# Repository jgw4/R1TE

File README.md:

# Replica-1-TE

This repository is a fork of The Original Replica 1 TE-3, with the addition of a KiCad re-building of the PCB using the native schematic and and pcb editors. This makes it easier for those willing to modify the Replica-1 to suit their particular custom replica-1. This repo will eventually become the basis for the uA1 stripped down Apple-1 clone.

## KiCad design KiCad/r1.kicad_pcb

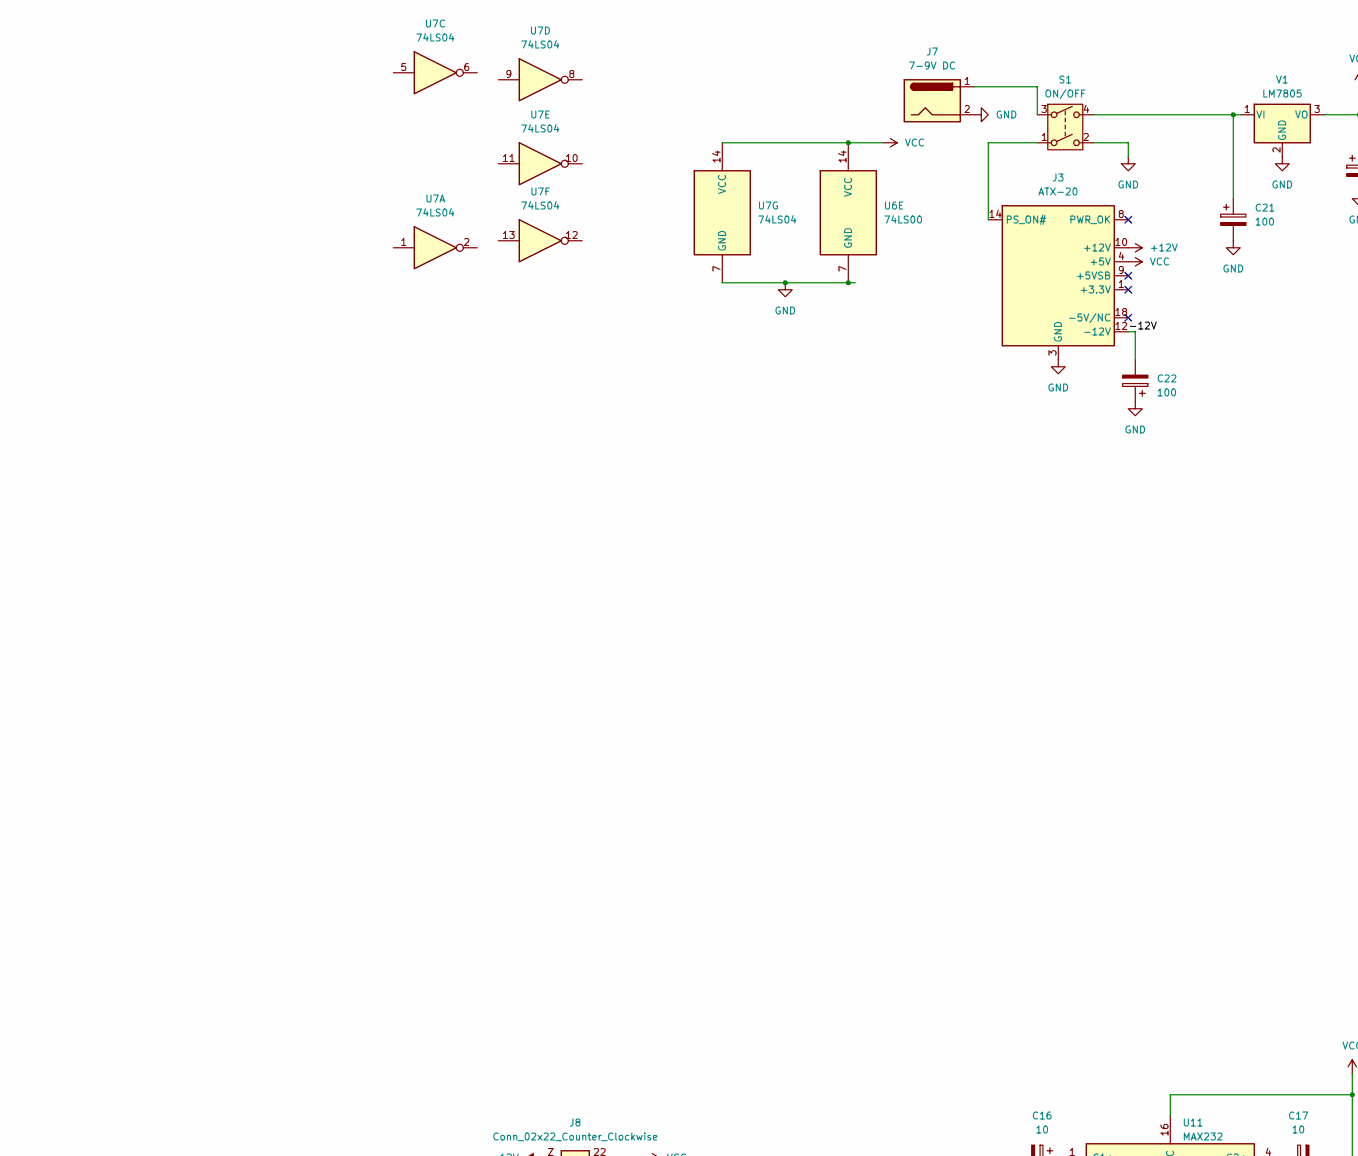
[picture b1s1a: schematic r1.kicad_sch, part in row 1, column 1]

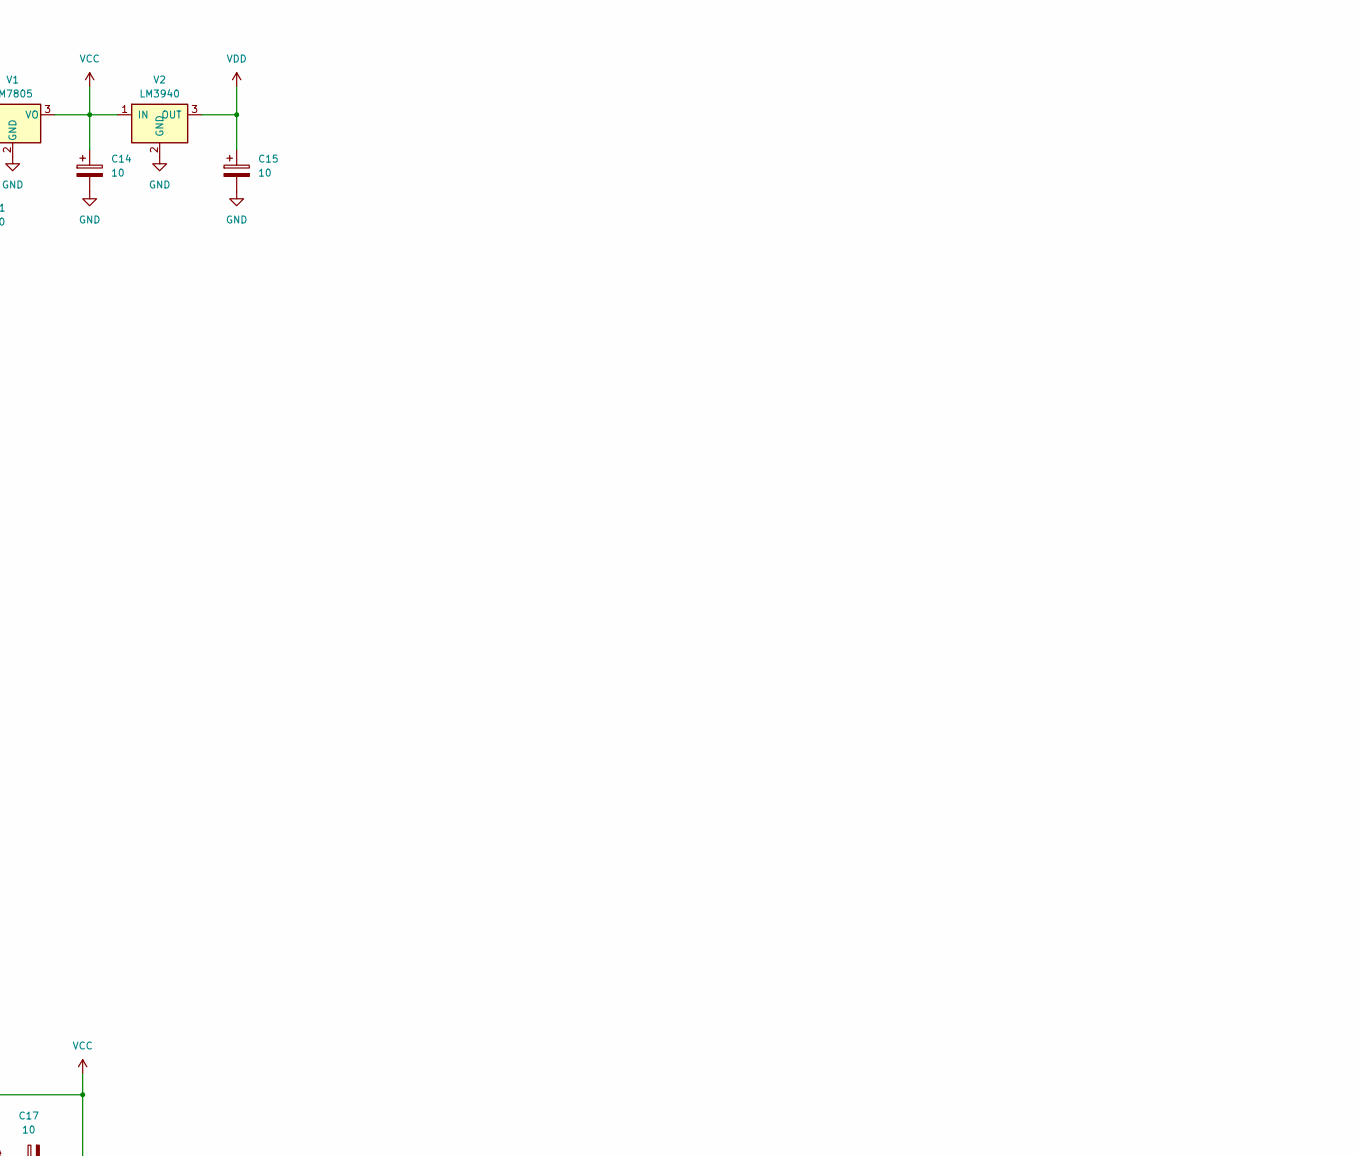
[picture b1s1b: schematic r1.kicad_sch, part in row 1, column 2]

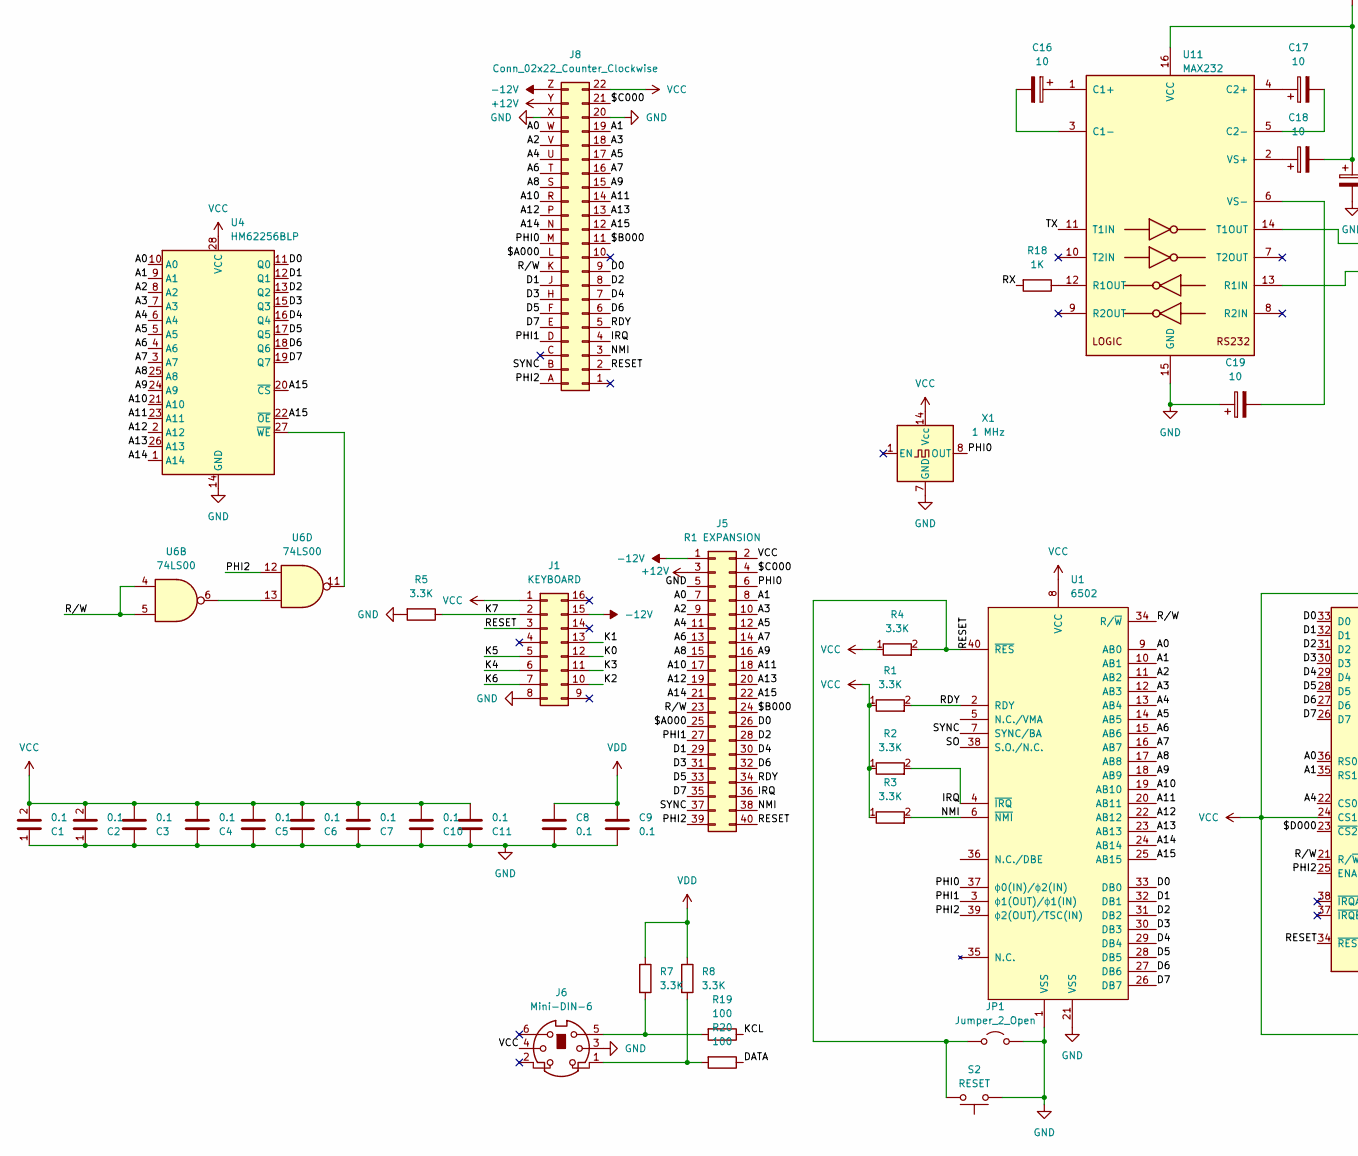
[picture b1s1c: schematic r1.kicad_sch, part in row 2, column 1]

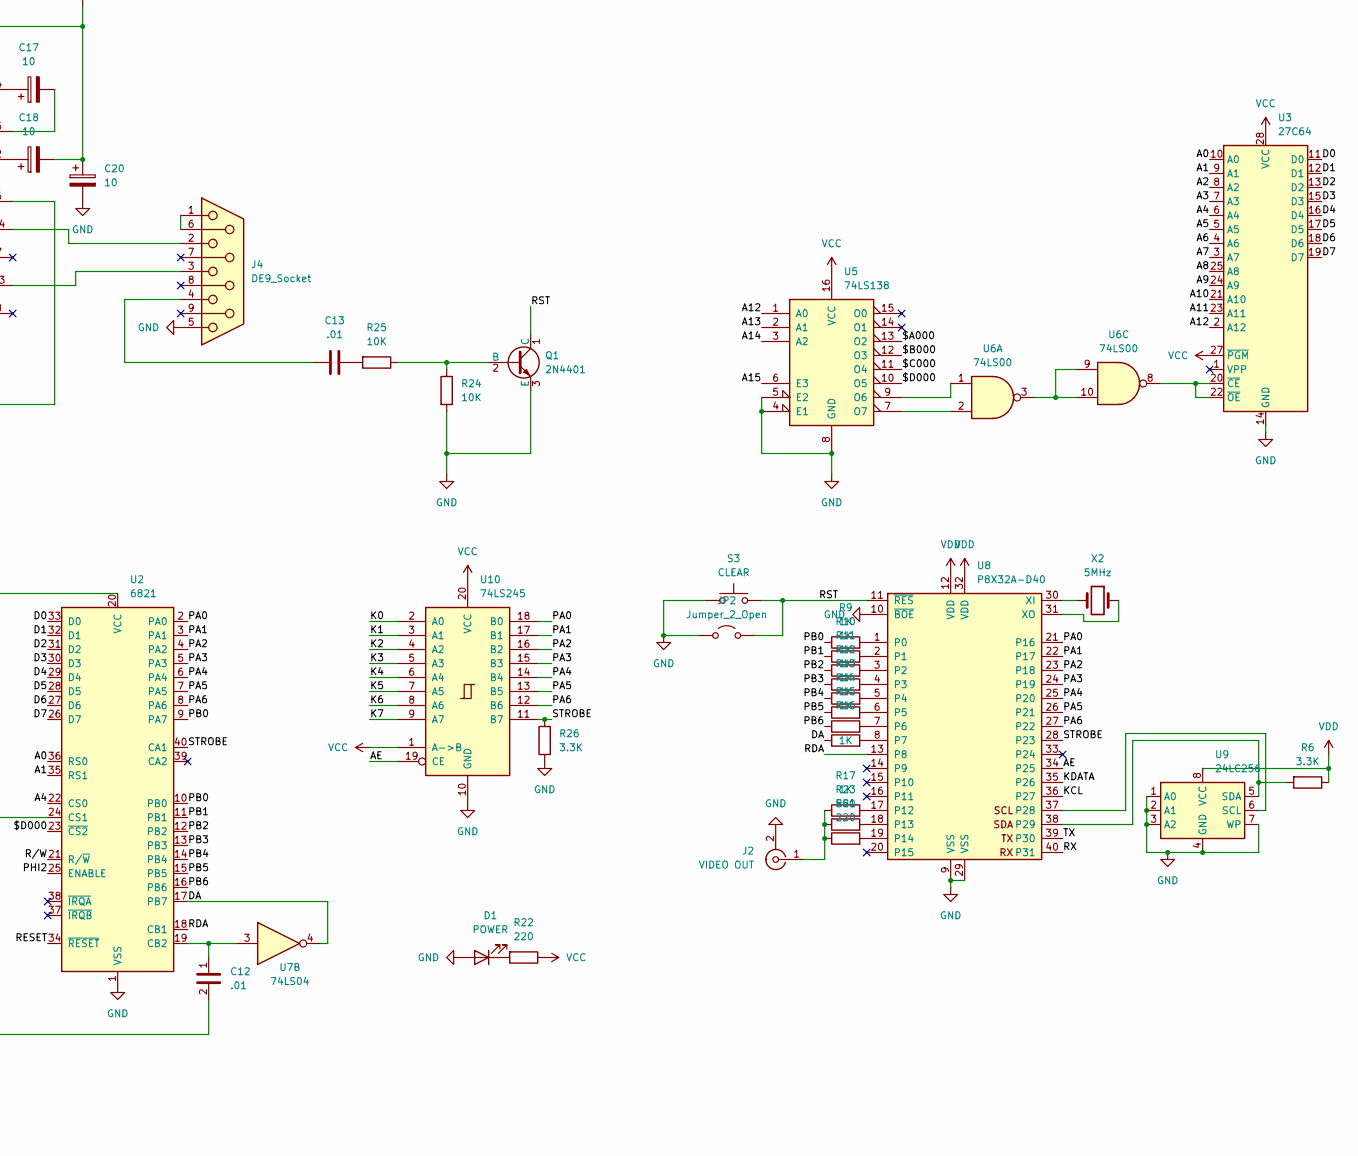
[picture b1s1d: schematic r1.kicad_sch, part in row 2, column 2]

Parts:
C1, C2, C3, C4, C5, C6, C7, C8, C9, C10, C11: 0.1; C_Disc_D7.0mm_W2.5mm_P5.00mm
C12, C13: .01; C_Disc_D7.0mm_W2.5mm_P5.00mm
C14, C15, C16, C17, C18, C19, C20: 10; CP_Radial_D5.0mm_P2.00mm
C21: 100; CP_Radial_D10.0mm_P5.00mm
C22: 100; CP_Radial_D5.0mm_P2.00mm
D1: POWER; LED_D5.0mm
J1: KEYBOARD; DIP-16_W7.62mm_Socket_LongPads
J2: VIDEO OUT; Keystone 901
J3: ATX-20; Molex_Mini-Fit_Jr_5566-20A2_2x10_P4.20mm_Vertical
J4: DE9_Socket; DSUB-9_Socket_Horizontal_P2.77x2.84mm_EdgePinOffset7.70mm_H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
J5: R1 EXPANSION; PinHeader_2x20_P2.54mm_Vertical
J6: Mini-DIN-6
J7: 7-9V DC; BarrelJack_GCT_DCJ200-10-A_Horizontal
J8: Conn_02x22_Counter_Clockwise; CardEdgeConnector_44p_P156mils
JP1, JP2: Jumper_2_Open; TestPoint_Bridge_Pitch2.54mm_Drill1.0mm
Q1: 2N4401; TO-92_Inline_Wide
R1, R2, R3, R4, R5, R6, R7, R8, R26: 3.3K; R_Axial_DIN0207_L6.3mm_D2.5mm_P10.16mm_Horizontal
R9, R10, R11, R12, R13, R14, R15, R16, R17, R18: 1K; R_Axial_DIN0207_L6.3mm_D2.5mm_P10.16mm_Horizontal
R19, R20: 100; R_Axial_DIN0207_L6.3mm_D2.5mm_P10.16mm_Horizontal
R21, R22: 220; R_Axial_DIN0207_L6.3mm_D2.5mm_P10.16mm_Horizontal
R23: 560; R_Axial_DIN0207_L6.3mm_D2.5mm_P10.16mm_Horizontal
R24, R25: 10K; R_Axial_DIN0207_L6.3mm_D2.5mm_P10.16mm_Horizontal
S1: ON/OFF; ToggleSW_DPDT_VerticalPC
S2: RESET; SW_PUSH_6mm
S3: CLEAR; SW_PUSH_6mm
U1: 6502; DIP-40_W15.24mm_Socket_LongPads
U2: 6821; DIP-40_W15.24mm_Socket_LongPads
U3: 27C64; DIP-28_W15.24mm_Socket_LongPads
U4: HM62256BLP; DIP-28_W15.24mm_Socket_LongPads
U5: 74LS138; DIP-16_W7.62mm_Socket_LongPads
U6: 74LS00; DIP-14_W7.62mm_Socket_LongPads
U7: 74LS04; DIP-14_W7.62mm_Socket_LongPads
U8: P8X32A-D40; DIP-40_W15.24mm_Socket_LongPads
U9: 24LC256; DIP-8_W7.62mm_Socket_LongPads
U10: 74LS245; DIP-20_W7.62mm_Socket_LongPads
U11: MAX232; DIP-16_W7.62mm_Socket_LongPads
V1: LM7805; TO-220-3_Horizontal_TabDown
V2: LM3940; TO-220-3_Horizontal_TabDown
X1: 1 MHz; Oscillator_DIP-14
X2: 5MHz; Crystal_HC18-U_Vertical

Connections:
+12V: J3.10 (+12V), J5.3, J8.Y
-12V: C22.2, J1.15, J3.12 (-12V), J5.1, J8.Z
/$A000: J5.25, J8.L (Pin_3L), U5.13 (O2)
/$B000: J5.24, J8.11, U5.12 (O3)
/$C000: J5.4, J8.21, U5.11 (O4)
/$D000: U2.23 (~CS2), U5.10 (O5)
/A0: J5.7, J8.W, U1.9 (AB0), U2.36 (RS0), U3.10 (A0), U4.10 (A0)
/A1: J5.8, J8.19, U1.10 (AB1), U2.35 (RS1), U3.9 (A1), U4.9 (A1)
/A2: J5.9, J8.V, U1.11 (AB2), U3.8 (A2), U4.8 (A2)
/A3: J5.10, J8.18, U1.12 (AB3), U3.7 (A3), U4.7 (A3)
/A4: J5.11, J8.U, U1.13 (AB4), U2.22 (CS0), U3.6 (A4), U4.6 (A4)
/A5: J5.12, J8.17, U1.14 (AB5), U3.5 (A5), U4.5 (A5)
/A6: J5.13, J8.T, U1.15 (AB6), U3.4 (A6), U4.4 (A6)
/A7: J5.14, J8.16, U1.16 (AB7), U3.3 (A7), U4.3 (A7)
/A8: J5.15, J8.S, U1.17 (AB8), U3.25 (A8), U4.25 (A8)
/A9: J5.16, J8.15, U1.18 (AB9), U3.24 (A9), U4.24 (A9)
/A10: J5.17, J8.R, U1.19 (AB10), U3.21 (A10), U4.21 (A10)
/A11: J5.18, J8.14, U1.20 (AB11), U3.23 (A11), U4.23 (A11)
/A12: J5.19, J8.P, U1.22 (AB12), U3.2 (A12), U4.2 (A12), U5.1 (A0)
/A13: J5.20, J8.13, U1.23 (AB13), U4.26 (A13), U5.2 (A1)
/A14: J5.21, J8.N, U1.24 (AB14), U4.1 (A14), U5.3 (A2)
/A15: J5.22, J8.12, U1.25 (AB15), U4.20 (~CS), U4.22 (~OE), U5.6 (E3)
/AE: U8.34 (P25), U10.19 (CE)
/D0: J5.26, J8.9, U1.33 (DB0), U2.33 (D0), U3.11 (D0), U4.11 (Q0)
/D1: J5.29, J8.J, U1.32 (DB1), U2.32 (D1), U3.12 (D1), U4.12 (Q1)
/D2: J5.28, J8.8, U1.31 (DB2), U2.31 (D2), U3.13 (D2), U4.13 (Q2)
/D3: J5.31, J8.H, U1.30 (DB3), U2.30 (D3), U3.15 (D3), U4.15 (Q3)
/D4: J5.30, J8.7, U1.29 (DB4), U2.29 (D4), U3.16 (D4), U4.16 (Q4)
/D5: J5.33, J8.F, U1.28 (DB5), U2.28 (D5), U3.17 (D5), U4.17 (Q5)
/D6: J5.32, J8.6, U1.27 (DB6), U2.27 (D6), U3.18 (D6), U4.18 (Q6)
/D7: J5.35, J8.E, U1.26 (DB7), U2.26 (D7), U3.19 (D7), U4.19 (Q7)
/DA: R16.1, U2.17 (PB7), U7.4
/DATA: R20.1
/IRQ: J5.36, J8.4, R2.2, U1.4 (~IRQ)
/K0: J1.12, U10.2 (A0)
/K1: J1.13, U10.3 (A1)
/K2: J1.10, U10.4 (A2)
/K3: J1.11, U10.5 (A3)
/K4: J1.6, U10.6 (A4)
/K5: J1.5, U10.7 (A5)
/K6: J1.7, U10.8 (A6)
/K7: J1.2, R5.1, U10.9 (A7)
/KCL: R19.1, U8.36 (P27)
/KDATA: U8.35 (P26)
/NMI: J5.38, J8.3, R3.2, U1.6 (~NMI)
/PA0: U2.2 (PA0), U8.21 (P16), U10.18 (B0)
/PA1: U2.3 (PA1), U8.22 (P17), U10.17 (B1)
/PA2: U2.4 (PA2), U8.23 (P18), U10.16 (B2)
/PA3: U2.5 (PA3), U8.24 (P19), U10.15 (B3)
/PA4: U2.6 (PA4), U8.25 (P20), U10.14 (B4)
/PA5: U2.7 (PA5), U8.26 (P21), U10.13 (B5)
/PA6: U2.8 (PA6), U8.27 (P22), U10.12 (B6)
/PB0: R9.1, U2.9 (PA7), U2.10 (PB0)
/PB1: R10.1, U2.11 (PB1)
/PB2: R11.1, U2.12 (PB2)
/PB3: R12.1, U2.13 (PB3)
/PB4: R13.1, U2.14 (PB4)
/PB5: R14.1, U2.15 (PB5)
/PB6: R15.1, U2.16 (PB6)
/PHI0: J5.6, J8.M, U1.37 (ɸ0(IN)/ɸ2(IN)), X1.8 (OUT)
/PHI1: J5.27, J8.D, U1.3 (ɸ1(OUT)/ɸ1(IN))
/PHI2: J5.39, J8.A, U1.39 (ɸ2(OUT)/TSC(IN)), U2.25 (ENABLE), U6.12
/RDA: U2.18 (CB1), U8.13 (P8)
/RDY: J5.34, J8.5, R1.2, U1.2 (RDY)
/RESET: J1.3, J5.40, J8.2, JP1.1 (A), R4.2, S2.2, U1.40 (~RES), U2.34 (~RESET)
/RST: JP2.2 (B), Q1.1 (C), S3.2, U8.11 (~RES)
/RX: R18.2, U8.40 (P31)
/R/W: J5.23, J8.K, U1.34 (R/~W), U2.21 (R/~W), U6.4, U6.5
/SO: U1.38 (S.O./N.C.)
/STROBE: R26.2, U2.40 (CA1), U8.28 (P23), U10.11 (B7)
/SYNC: J5.37, J8.B (PinB), U1.7 (SYNC/BA)
/TX: U8.39 (P30), U11.11 (T1IN)
GND: C1.1, C2.1, C3.1, C4.1, C5.1, C6.1, C7.1, C8.1, C9.1, C10.1, C11.1, C14.2, C15.2, C19.1, C20.2, C21.2, C22.1, D1.2 (A), J1.8, J2.2 (Ext), J3.3 (GND), J3.5 (GND), J3.7 (GND), J3.13 (GND), J3.15 (GND), J3.16 (GND), J3.17 (GND), J4.5, J5.5, J6.3, J7.2, J8.20, J8.X, JP1.2 (B), JP2.1 (A), Q1.3 (E), R5.2, R24.2, R26.1, S1.2, S2.1, S3.1, U1.1 (VSS), U1.21 (VSS), U2.1 (VSS), U3.14 (GND), U4.14 (GND), U5.4 (E1), U5.5 (E2), U5.8 (GND), U6.7 (GND), U7.7 (GND), U8.9 (VSS), U8.10 (~BOE), U8.29 (VSS), U9.1 (A0), U9.2 (A1), U9.3 (A2), U9.4 (GND), U9.7 (WP), U10.10 (GND), U11.15 (GND), V1.2 (GND), V2.2 (GND), X1.7 (GND)
unnamed: C13.1, J4.4
unnamed: C13.2, R25.2
unnamed: D1.1 (K), R22.2
unnamed: J2.1 (In), R17.1, R21.1, R23.1
unnamed: J3.14 (PS_ON#), S1.1
unnamed: J4.1, J4.6
unnamed: J6.1, R8.2, R20.2
unnamed: J6.5, R7.2, R19.2
unnamed: J7.1, S1.3
unnamed: Q1.2 (B), R24.1, R25.1
unnamed: C12.1, U2.19 (CB2), U7.3
unnamed: U3.20 (~CE), U3.22 (~OE), U6.8
unnamed: U4.27 (~WE), U6.11
unnamed: U5.9 (O6), U6.1
unnamed: U5.7 (O7), U6.2
unnamed: U6.3, U6.9, U6.10
unnamed: U6.6, U6.13
unnamed: R9.2, U8.1 (P0)
unnamed: R10.2, U8.2 (P1)
unnamed: R11.2, U8.3 (P2)
unnamed: R12.2, U8.4 (P3)
unnamed: R13.2, U8.5 (P4)
unnamed: R14.2, U8.6 (P5)
unnamed: R15.2, U8.7 (P6)
unnamed: R16.2, U8.8 (P7)
unnamed: R17.2, U8.17 (P12)
unnamed: R23.2, U8.18 (P13)
unnamed: R21.2, U8.19 (P14)
unnamed: U8.37 (P28), U9.6 (SCL)
unnamed: R6.2, U8.38 (P29), U9.5 (SDA)
unnamed: U8.30 (XI), X2.2
unnamed: U8.31 (XO), X2.1
unnamed: C16.1, U11.1 (C1+)
unnamed: C16.2, U11.3 (C1-)
unnamed: C17.1, U11.4 (C2+)
unnamed: C17.2, U11.5 (C2-)
unnamed: J4.3, U11.13 (R1IN)
unnamed: R18.1, U11.12 (R1OUT)
unnamed: J4.2, U11.14 (T1OUT)
unnamed: C18.1, U11.2 (VS+)
unnamed: C19.2, U11.6 (VS-)
unnamed: C21.1, S1.4, V1.1 (VI)
VCC: C1.2, C2.2, C3.2, C4.2, C5.2, C6.2, C7.2, C10.2, C11.2, C12.2, C14.1, C18.2, C20.1, J1.1, J3.4 (+5V), J3.6 (+5V), J3.19 (+5V), J3.20 (+5V), J5.2, J6.4, J8.22, R1.1, R2.1, R3.1, R4.1, R22.1, U1.8 (VCC), U2.20 (VCC), U2.24 (CS1), U3.27 (~PGM), U3.28 (VCC), U4.28 (VCC), U5.16 (VCC), U6.14 (VCC), U7.14 (VCC), U10.1 (A->B), U10.20 (VCC), U11.16 (VCC), V1.3 (VO), V2.1 (IN), X1.14 (Vcc)
VDD: C8.2, C9.2, C15.1, R6.1, R7.1, R8.1, U8.12 (VDD), U8.32 (VDD), U9.8 (VCC), V2.3 (OUT)

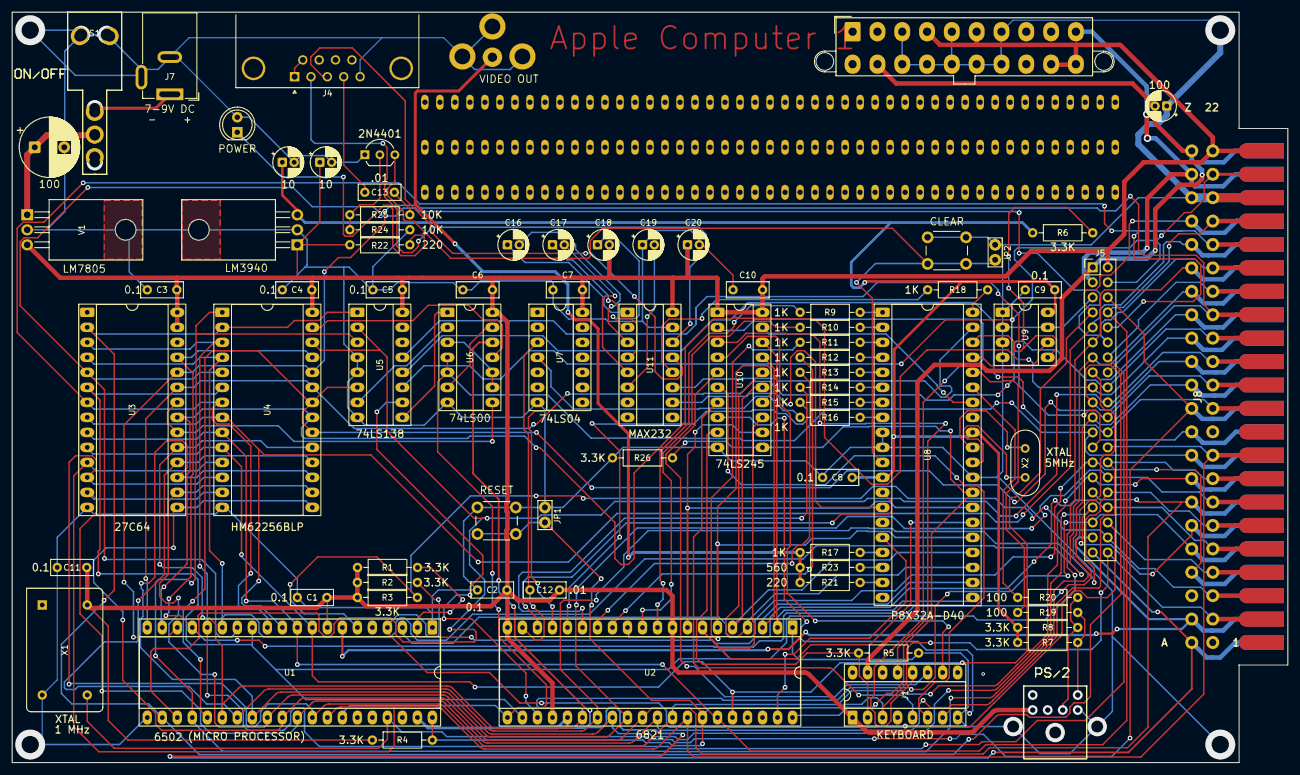
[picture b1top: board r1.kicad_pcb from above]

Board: 2 copper layers, 215.9 x 127.0 mm, 77 parts (0 on the bottom side), 114 nets.
